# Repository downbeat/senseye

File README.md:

# SensEye

SensEye is a low-power, wireless gaze detection system.

## SensEye v1 and v2

[SensEye v1](SENSEYE_V1.md) is a fully implemented prototype wireless eyetracker system based on cloud offloading and machine learning.  SensEye v2 is the started, incomplete, [but not abandonded](https://github.com/lab11/SensEye-2), second generation eye tracking capture platform, capable of streaming data from two imagers at 29 frames-per-second (FPS) over a pseudo-HTTP 1.0 interface.

## Authors

SensEye v1 is the work of Joe Romeo, Justin Paupore and me, Russ Bielawski.  SensEye v2, insofar as it existed within the time frame of this repository, is my sole, personal work as a Graduate Student Research Assistant (GSRA) of [Prabal Dutta](https://web.eecs.umich.edu/~prabal)'s in 2012-2013.

## Major git Repo Reorganization

The SensEye git repository was, for a long time, in need of serious reorganization.  In addition to reorganization, I took the opportunity to finish a few things (I couldn't resist).

I have done some pretty gnarly hacking on the git repository, up to and including using <a href="https://help.github.com/articles/remove-sensitive-data/">filter-branch</a> to permanently purge irrelevant data which should have never been stored in the source repo in the first place.

**If you have an old SensEye git repository cloned prior to 2015, you must peform a rebase or clone the repo anew.**

## Repository Organization

The root of the SensEye repository is split into `hardware` and `software` subdirectories.  Any technical documentation is intermingled (generally in the form of README files).  Under both `hardware` and `software`, there are three directories: `common`, `v1` and `v2`.  The distinction between what goes in these directories should be clear: SensEye v1 artifacts are found in `v1`, SensEye v2 artifacts are found in `v2` and artifacts which are common to both are in found in `common`.

## Frontend Software

The so called "frontend" software is the software that runs on a PC or smartphone connected to the glasses with Bluetooth (or USB).  Most of the frontend code for SensEye is not v1 or v2 specific, with the exception of the so-called "capture frontends" for each, which receive the data from the capture hardware and output it over stdout according to the Glasses Data Protocol (GDP).  The common frontend code is found in [/software/common/frontends/](software/common/frontends/).  The PC frontend code was written for Linux, but most seems to build and run fine on OS X with OpenCV installed via MacPorts.

### Running the PC Frontend Code

The frontends are connected to one another via [pipes](https://en.wikipedia.org/wiki/Pipeline_%28Unix%29) communicating (unidirectionally) over the Glasses Data Protocol (GDP).  To understand what a particular frontend does, read the help text for that program.  As a simple (and common) example, the following command will capture data from SensEye glasses and both display the images on the screen and record the capture to disk in Glasses Data Exchange Formate (GDF):

    glasses_capture | tee >(glasses_display) | glasses_record -o <path>

#### The SensEye Demo

**Sadly, the demo crashes on OS X.  See [http://code.opencv.org/issues/2846](http://code.opencv.org/issues/2846).**

To run the demo:

    glasses_capture | demo

For a description of how to use the demo, see [http://energy.eecs.umich.edu/wiki/doku.php?id=proj:insight:insight_linux_utils](http://energy.eecs.umich.edu/wiki/doku.php?id=proj:insight:insight_linux_utils).

#### Other platforms

##### Android

When SensEye was conceived, it was envisioned that smartphones would be used as the powerful co-processing device to perform the really processor and memory intensive operations (such as the machine learning classifier).  A simple proof-of-concept capture frontend (called "frame grabber") was developed for Android, and is found in the repository at [/software/v1/capture_frontend/android](software/v1/capture_frontend/android).  Most of the interesting data processing frontend software was written for a Linux PC because it was the easiest way to make the most progress as quickly as possible.

#### Etymology of the Label "Frontend" Software

Admittedly, calling this the "frontend" software seems backwards.  A better name might be "cloud" software, but even that isn't quite evocative enough.  In the usual case, the cloud portion of an offloading application is called the "backend."  However, the situation with offloading *to* a smartphone muddles this conceptually.  Because the feedback to the user (at least in the SensEye prototype) is provided via the front-end software running on a device with a screen.

### Data Processing Interchange Protocol and Frontends

Frontends (for *nix), such as glasses_display, glasses_record and capture_replay, utilize the Glasses Data Protocol (GDP) v1 (or, pre-v1, called v0) to pass data between one another.

During the cleanup of this repository, I took time to formalize the protocol and data exchange (recoreded file on disk) formats.  Glasses Data Protocol (GDP) v1 and Glasses Data Exchange Format (GDF) v1 are both implemented in a C library, libglasses2.  This formalization of the previously not-formal protocol makes as few changes as possible to allow painless adaptation of existing code. 

#### Limitations of the Protocol 

The data processing protocol is fine for exchanging image data between data processing programs (frontends) in grayscale.  However, the protocol lacks any support for color images or scalar data such as the known gaze location, which it really needs in order to support all the non-standard features of the existing frontends in a standardized way.

## Funding

SensEye was supported by the National Science Foundation, NSF Grant 1239341.

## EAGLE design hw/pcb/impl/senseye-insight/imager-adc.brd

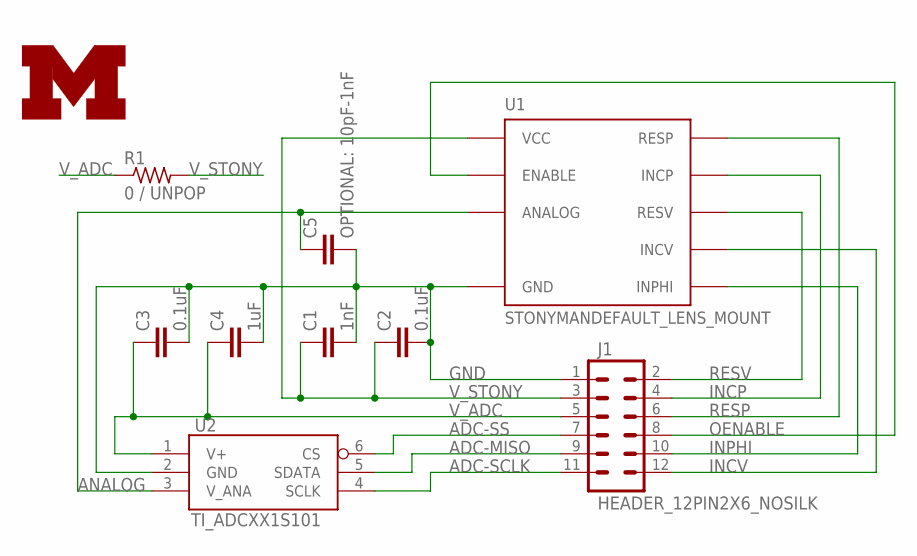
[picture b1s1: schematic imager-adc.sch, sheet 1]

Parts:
C1: 1nF; C0603; DIGIKEY 1276-1916-2-ND
C2, C3: 0.1uF; C0603; DIGIKEY 1276-1012-2-ND
C4: 1uF; C0603; DIGIKEY 1276-1243-2-ND
C5: OPTIONAL: 10pF-1nF; C0603; DIGIKEY 1276-1187-6-ND
J1: HEADER_12PIN2X6_NOSILK; HEADER2X6/0.05IN_NO_SILK; DIGIKEY S9015E-06-ND
R1: 0 / UNPOP; R0603; DIGIKEY 1276-3510-6-ND
U1: STONYMANDEFAULT_LENS_MOUNT; STONYMAN_DEFAULT_LENS
U2: TI_ADCXX1S101; SOT23-6; DIGIKEY ADC121S101CIMF/NOPBDKR-ND
U$1: UMICH_SOLID_SMALL; UMICH_SOLID_75MIL

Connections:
ADC-MISO: J1.9, U2.5 (SDATA)
ADC-SCLK: J1.11, U2.4 (SCLK)
ADC-SS: J1.7, U2.6 (CS)
ANALOG: C5.1, U1.P$8 (ANALOG), U2.3 (V_ANA)
GND: C1.2, C2.2, C3.2, C4.2, C5.2, J1.1, U1.P$1 (GND), U1.P$10 (GND), U2.2 (GND)
INCP: J1.4, U1.P$4 (INCP)
INCV: J1.12, U1.P$6 (INCV)
INPHI: J1.10, U1.P$7 (INPHI)
OENABLE: J1.8, U1.P$9 (ENABLE)
RESP: J1.6, U1.P$3 (RESP)
RESV: J1.2, U1.P$5 (RESV)
V_ADC: C3.1, C4.1, J1.5, R1.1, U2.1 (V+)
V_STONY: C1.1, C2.1, J1.3, R1.2, U1.P$2 (VCC)

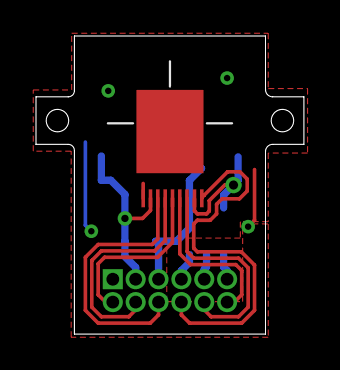
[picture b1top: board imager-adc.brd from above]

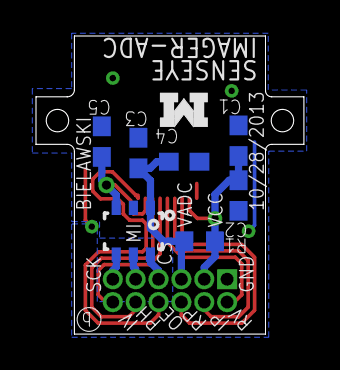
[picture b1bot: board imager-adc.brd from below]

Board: 2 copper layers, 14.9 x 16.6 mm, 10 parts (8 on the bottom side), 13 nets.

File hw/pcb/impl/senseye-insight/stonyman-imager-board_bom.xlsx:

Part | Value | Device | Package | DIGIKEY | Description
C1 | 1nF | C-EUC0603 | C0603 | 1276-1916-2-ND | CAPACITOR, European symbol
C2 | 0.1uF | C-EUC0603 | C0603 | 1276-1012-2-ND | CAPACITOR, European symbol
C3 | 0.1uF | C-EUC0603 | C0603 | 1276-1012-2-ND | CAPACITOR, European symbol
C4 | 1uF | C-EUC0603 | C0603 | 1276-1243-2-ND | CAPACITOR, European symbol
C5 | OPTIONAL: 10pF-1nF | C-EUC0603 | C0603 | 1276-1187-6-ND | CAPACITOR, European symbol
J1 | HEADER_12PIN2X6_NOSILK | HEADER_12PIN2X6_NOSILK | HEADER2X6/0.05IN_NO_SILK | S9015E-06-ND
R1 | 0 / UNPOP | R-US_R0603 | R0603 | 1276-3510-6-ND | RESISTOR, American symbol
U1 | STONYMANDEFAULT_LENS_MOUNT | STONYMANDEFAULT_LENS_MOUNT | STONYMAN_DEFAULT_LENS |  | Centeye Stonyman imager chip
U2 | TI_ADCXX1S101 | TI_ADCXX1S101 | SOT23-6 | ADC121S101CIMF/NOPBDKR-ND | Texas Instruments ADCXX1S101 (ADC081S101, ADC101S101, ADC121S101) Single Channe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

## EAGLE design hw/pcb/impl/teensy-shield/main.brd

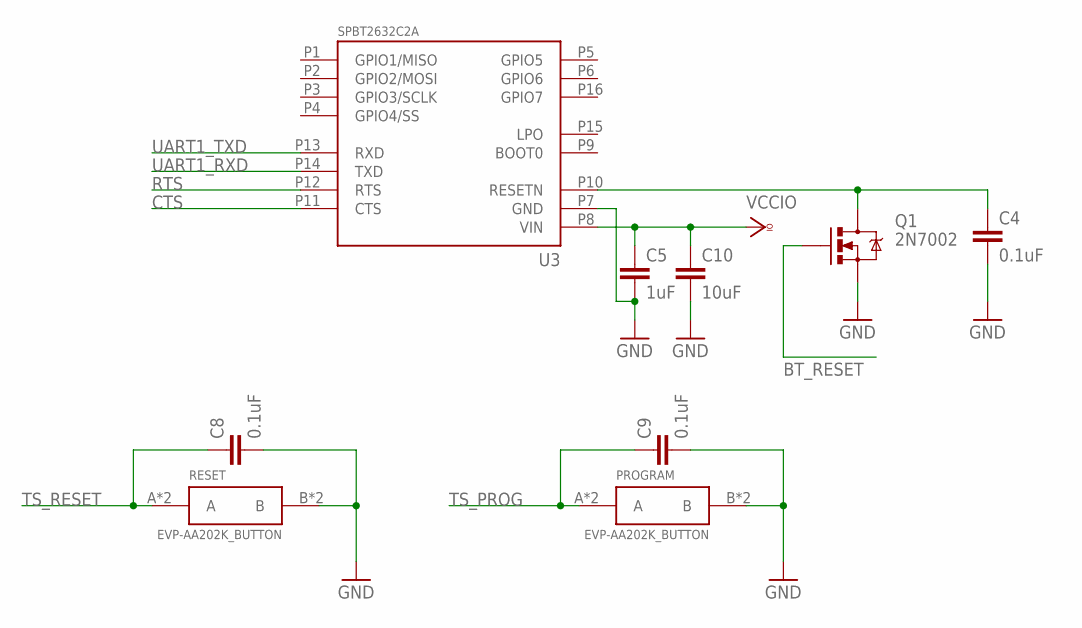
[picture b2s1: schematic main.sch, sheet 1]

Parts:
C4: 0.1uF; C0402
C5: 1uF; C0402
C8, C9: 0.1uF; C0603
C10: 10uF; C0603@1
PROGRAM: EVP-AA202K_BUTTON; EVP-AA202K_4PIN
Q1: 2N7002; SOT23-3
RESET: EVP-AA202K_BUTTON; EVP-AA202K_4PIN
U3: SPBT2632C2A; SPBT2632C2A_16PIN_SMD

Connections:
BT_RESET: Q1.1 (G); also elsewhere on the board
CTS: U3.P11 (CTS); also elsewhere on the board
GND: C4.2, C5.2, C8.2, C9.2, C10.2, PROGRAM.B, PROGRAM.B' (B), Q1.2 (S), RESET.B, RESET.B' (B), U3.P7 (GND); also elsewhere on the board
unnamed: C4.1, Q1.3 (D), U3.P10 (RESETN)
RTS: U3.P12 (RTS); also elsewhere on the board
TS_PROG: C9.1, PROGRAM.A, PROGRAM.A' (A); also elsewhere on the board
TS_RESET: C8.1, RESET.A, RESET.A' (A); also elsewhere on the board
UART1_RXD: U3.P14 (TXD); also elsewhere on the board
UART1_TXD: U3.P13 (RXD); also elsewhere on the board
VCCIO: C5.1, C10.1, U3.P8 (VIN); also elsewhere on the board

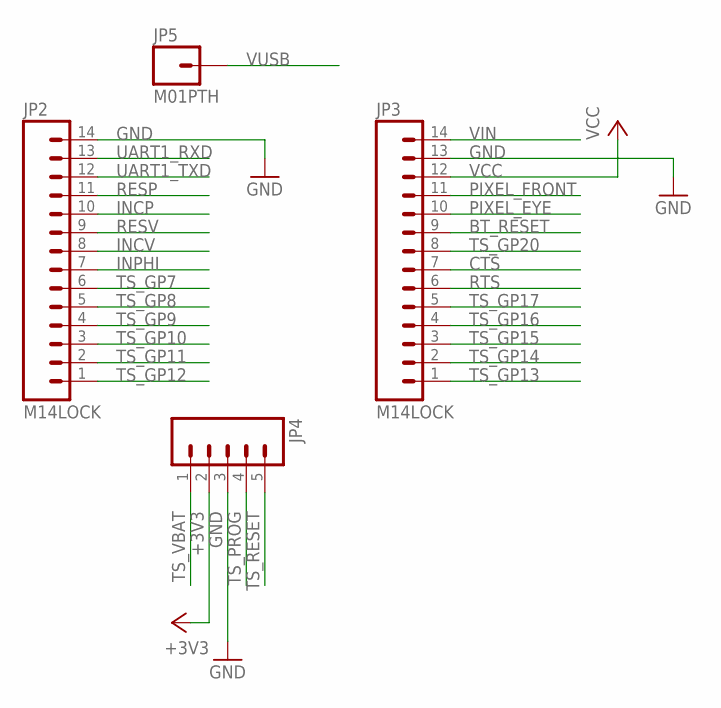
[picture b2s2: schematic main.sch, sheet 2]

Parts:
JP2, JP3: M14LOCK; 1X14_LOCK
JP4: M05LOCK; 1X05_LOCK
JP5: M01PTH; 1X01

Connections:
+3V3: JP4.2
BT_RESET: JP3.9; also elsewhere on the board
CTS: JP3.7; also elsewhere on the board
GND: JP2.14, JP3.13, JP4.3; also elsewhere on the board
INCP: JP2.10
INCV: JP2.8
INPHI: JP2.7
PIXEL_EYE: JP3.10
PIXEL_FRONT: JP3.11
RESP: JP2.11
RESV: JP2.9
RTS: JP3.6; also elsewhere on the board
TS_GP7: JP2.6
TS_GP8: JP2.5
TS_GP9: JP2.4
TS_GP10: JP2.3
TS_GP11: JP2.2
TS_GP12: JP2.1
TS_GP13: JP3.1
TS_GP14: JP3.2
TS_GP15: JP3.3
TS_GP16: JP3.4
TS_GP17: JP3.5
TS_GP20: JP3.8
TS_PROG: JP4.4; also elsewhere on the board
TS_RESET: JP4.5; also elsewhere on the board
TS_VBAT: JP4.1
UART1_RXD: JP2.13; also elsewhere on the board
UART1_TXD: JP2.12; also elsewhere on the board
VCC: JP3.12
VIN: JP3.14; also elsewhere on the board
VUSB: JP5.1; also elsewhere on the board

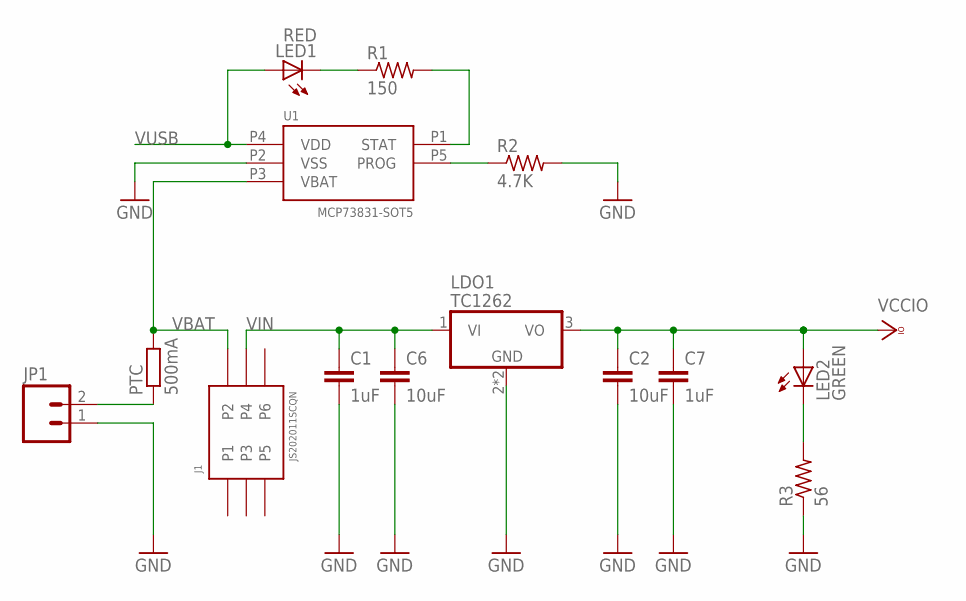
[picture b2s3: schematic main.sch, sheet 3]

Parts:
C1: 1uF; C0603
C2: 10uF; C0603
C6: 10uF; C0603@1
C7: 1uF; C0603@1
J1: JS202011SCQN; JS2020_6PIN_SMT
JP1: M02-JST-2MM-SMT; JST-2-SMD
LDO1: TC1262; SOT223
LED1: RED; CHIPLED_0603
LED2: GREEN; CHIPLED_0603
PTC: 500mA; R0402
R1: 150; R0402
R2: 4.7K; R0402
R3: 56; R0603
U1: MCP73831-SOT5; SOT23-5

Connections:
GND: C1.2, C2.2, C6.2, C7.2, JP1.1, LDO1.2 (GND), LDO1.4 (GND), R2.2, R3.1, U1.P2 (VSS); also elsewhere on the board
unnamed: LED1.C, R1.1
unnamed: R1.2, U1.P1 (STAT)
unnamed: R2.1, U1.P5 (PROG)
unnamed: JP1.2, PTC.1
unnamed: LED2.C, R3.2
VBAT: J1.P2, PTC.2, U1.P3 (VBAT)
VCCIO: C2.1, C7.1, LDO1.3 (VO), LED2.A; also elsewhere on the board
VIN: C1.1, C6.1, J1.P4, LDO1.1 (VI); also elsewhere on the board
VUSB: LED1.A, U1.P4 (VDD); also elsewhere on the board

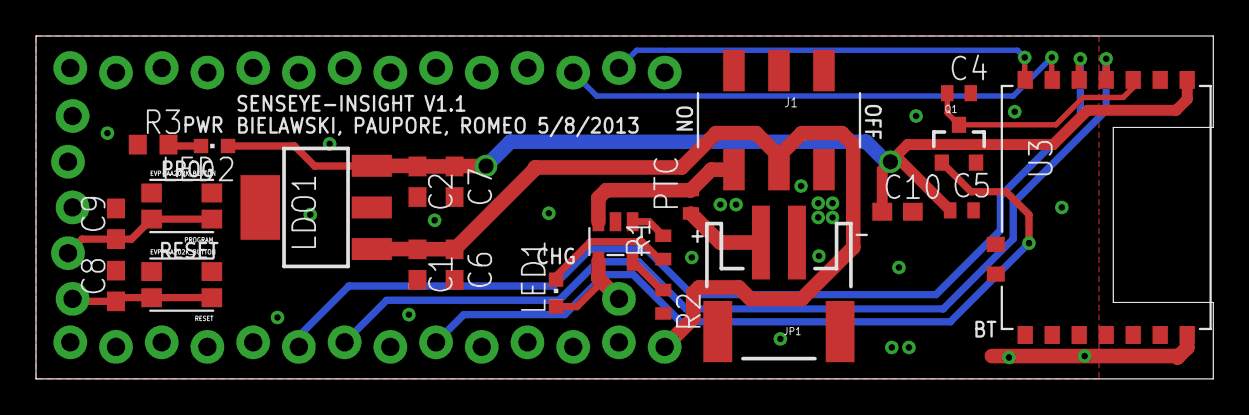
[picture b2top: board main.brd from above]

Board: 2 copper layers, 65.4 x 19.1 mm, 27 parts (0 on the bottom side), 18 nets.

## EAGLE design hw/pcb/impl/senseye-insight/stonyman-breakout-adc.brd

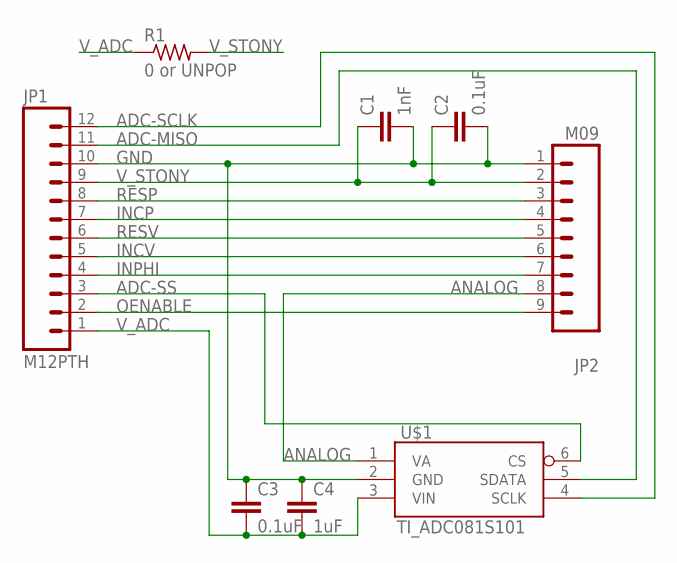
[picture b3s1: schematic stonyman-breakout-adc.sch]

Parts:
C1: 1nF; C0603
C2, C3: 0.1uF; C0603
C4: 1uF; C0603
JP1: M12PTH; 1X12
JP2: M09; 1X09
R1: 0 or UNPOP; R0603
U$1: TI_ADC081S101; SOT23-6

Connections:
ADC-MISO: JP1.11, U$1.5 (SDATA)
ADC-SCLK: JP1.12, U$1.4 (SCLK)
ADC-SS: JP1.3, U$1.6 (CS)
ANALOG: JP2.8, U$1.1 (VA)
GND: C1.2, C2.2, C3.1, C4.1, JP1.10, JP2.1, U$1.2 (GND)
INCP: JP1.7, JP2.4
INCV: JP1.5, JP2.6
INPHI: JP1.4, JP2.7
OENABLE: JP1.2, JP2.9
RESP: JP1.8, JP2.3
RESV: JP1.6, JP2.5
V_ADC: C3.2, C4.2, JP1.1, R1.1, U$1.3 (VIN)
V_STONY: C1.1, C2.1, JP1.9, JP2.2, R1.2

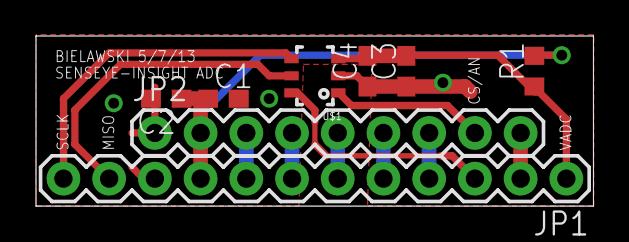
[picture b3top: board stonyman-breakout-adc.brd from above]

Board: 2 copper layers, 31.0 x 9.4 mm, 8 parts (0 on the bottom side), 13 nets.

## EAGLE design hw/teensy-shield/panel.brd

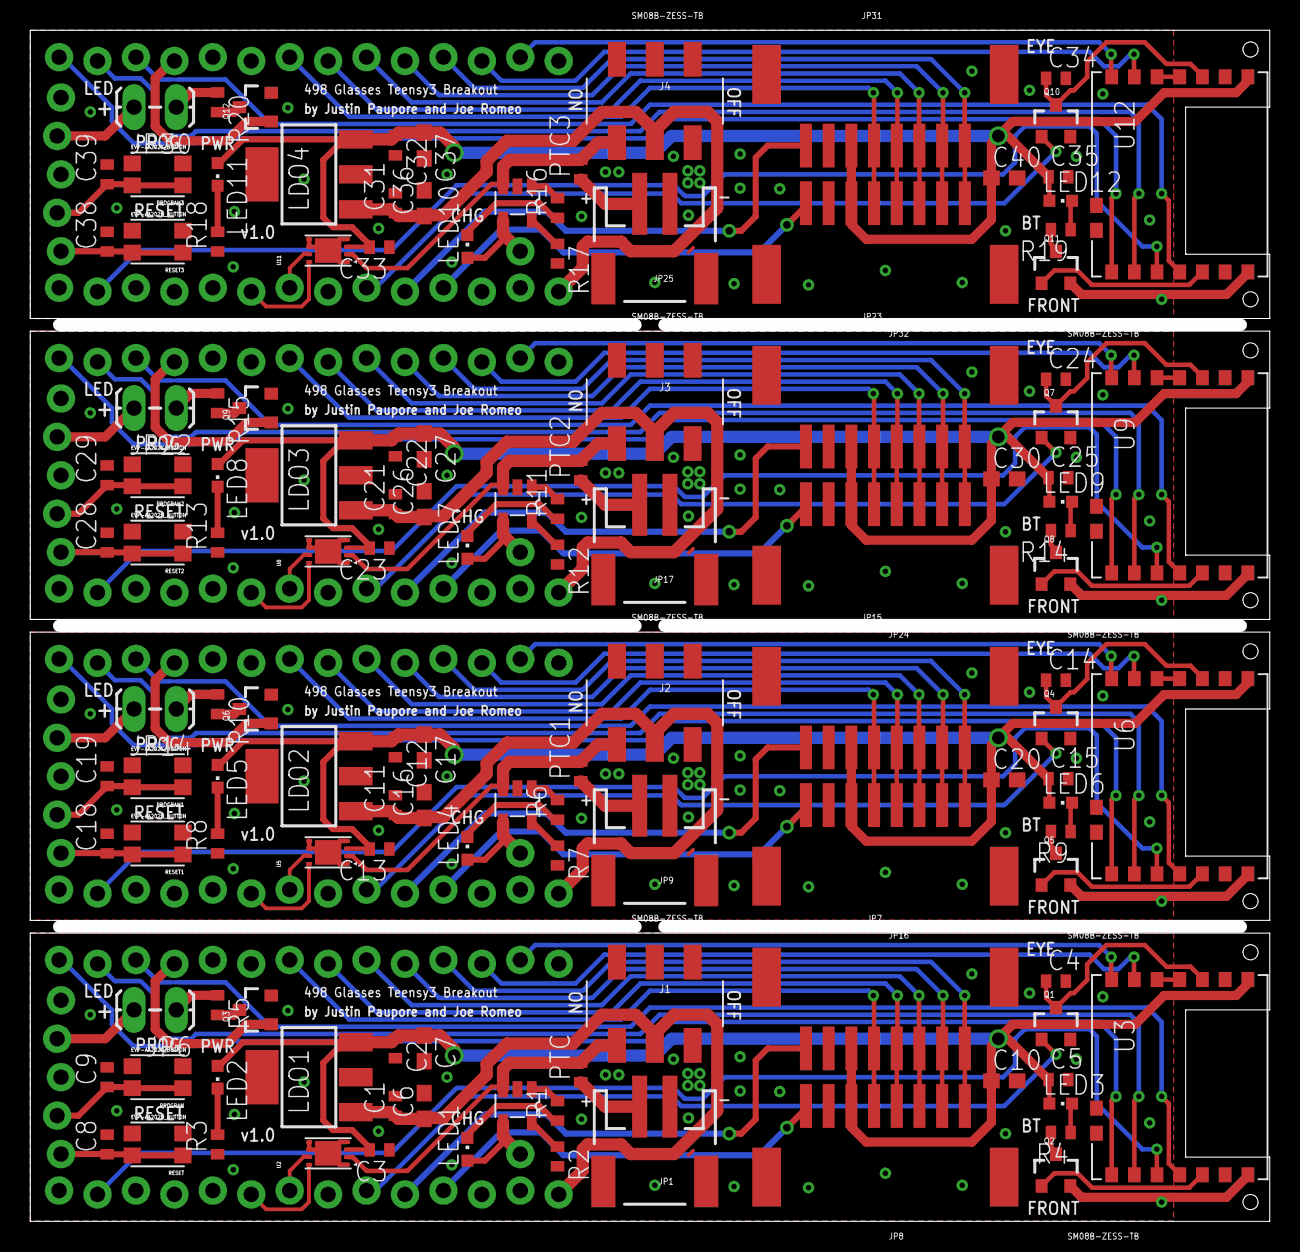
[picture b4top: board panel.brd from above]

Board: 2 copper layers, 81.1 x 77.9 mm, 148 parts (0 on the bottom side), 148 nets.

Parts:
C1, C2, C3, C5, C11, C12, C13, C15, C21, C22, C23, C25, C31, C32, C33, C35: 1uF; C0402
C4, C8, C9, C14, C18, C19, C24, C28, C29, C34, C38, C39: 0.1uF; C0402
C6, C7, C10, C16, C17, C20, C26, C27, C30, C36, C37, C40: 10uF; C0603
J1, J2, J3, J4: JS202011SCQN; JS2020_6PIN_SMT
JP1, JP9, JP17, JP25: JST-2-SMD
JP2, JP3, JP10, JP11, JP18, JP19, JP26, JP27: M14LOCK; 1X14_LOCK
JP4, JP12, JP20, JP28: 1X05_LOCK
JP5, JP13, JP21, JP29: M01PTH; 1X01
JP6, JP14, JP22, JP30: LED; 1X02_LOCK_LONGPADS
JP7, JP8, JP15, JP16, JP23, JP24, JP31, JP32: SM08B-ZESS-TB; SM08B_8PIN_SMD
LDO1, LDO2, LDO3, LDO4: TC1262; SOT223
LED1, LED4, LED7, LED10: RED; CHIPLED_0603
LED2, LED5, LED8, LED11: GREEN; CHIPLED_0603
LED3, LED6, LED9, LED12: BLUE; CHIPLED_0603
PROGRAM, PROGRAM1, PROGRAM2, PROGRAM3: EVP-AA202K_BUTTON; EVP-AA202K_4PIN
PTC, PTC1, PTC2, PTC3: 500mA; R0402
Q1, Q2, Q3, Q4, Q5, Q6, Q7, Q8, Q9, Q10, Q11, Q12: 2N7002; SOT23-3
R1, R6, R11, R16: 150; R0402
R2, R7, R12, R17: 4.7K; R0402
R3, R4, R8, R9, R13, R14, R18, R19: 56; R0402
R5, R10, R15, R20: DNI; R0402
RESET, RESET1, RESET2, RESET3: EVP-AA202K_BUTTON; EVP-AA202K_4PIN
U1, U4, U7, U10: MCP73831-SOT5; SOT23-5
U2, U5, U8, U11: MAX17040-TDFN; TDFN_8PIN
U3, U6, U9, U12: SPBT2632C2A; SPBT2632C2A_16PIN_SMD

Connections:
+3V1: JP12.2, JP14.2
+3V2: JP20.2, JP22.2
+3V3: JP4.2, JP6.2
+3V4: JP28.2, JP30.2
BT_RESET: JP3.9, Q1.1
BT_RESET1: JP11.9, Q4.1
BT_RESET2: JP19.9, Q7.1
BT_RESET3: JP27.9, Q10.1
GND: C1.2, C2.2, C3.1, C4.2, C5.2, C6.2, C7.2, C8.2, C9.2, C10.2, JP1.1, JP2.14, JP3.13, JP4.3, JP7.P7, JP8.P2, LDO1.2, LDO1.4, PROGRAM.B, PROGRAM.B', Q1.2, Q2.2, Q3.2, R2.2, R3.1, RESET.B, RESET.B', U1.P2, U2.EP, U2.P1, U2.P4, U2.P5, U2.P6, U3.P7
GND1: C11.2, C12.2, C13.1, C14.2, C15.2, C16.2, C17.2, C18.2, C19.2, C20.2, JP9.1, JP10.14, JP11.13, JP12.3, JP15.P7, JP16.P2, LDO2.2, LDO2.4, PROGRAM1.B, PROGRAM1.B', Q4.2, Q5.2, Q6.2, R7.2, R8.1, RESET1.B, RESET1.B', U4.P2, U5.EP, U5.P1, U5.P4, U5.P5, U5.P6, U6.P7
GND2: C21.2, C22.2, C23.1, C24.2, C25.2, C26.2, C27.2, C28.2, C29.2, C30.2, JP17.1, JP18.14, JP19.13, JP20.3, JP23.P7, JP24.P2, LDO3.2, LDO3.4, PROGRAM2.B, PROGRAM2.B', Q7.2, Q8.2, Q9.2, R12.2, R13.1, RESET2.B, RESET2.B', U7.P2, U8.EP, U8.P1, U8.P4, U8.P5, U8.P6, U9.P7
GND3: C31.2, C32.2, C33.1, C34.2, C35.2, C36.2, C37.2, C38.2, C39.2, C40.2, JP25.1, JP26.14, JP27.13, JP28.3, JP31.P7, JP32.P2, LDO4.2, LDO4.4, PROGRAM3.B, PROGRAM3.B', Q10.2, Q11.2, Q12.2, R17.2, R18.1, RESET3.B, RESET3.B', U10.P2, U11.EP, U11.P1, U11.P4, U11.P5, U11.P6, U12.P7
I2C_SCL: JP3.7, U2.P7
I2C_SCL1: JP11.7, U5.P7
I2C_SCL2: JP19.7, U8.P7
I2C_SCL3: JP27.7, U11.P7
I2C_SDA: JP3.6, U2.P8
I2C_SDA1: JP11.6, U5.P8
I2C_SDA2: JP19.6, U8.P8
I2C_SDA3: JP27.6, U11.P8
INCP: JP2.10, JP7.P2, JP8.P7
INCP1: JP10.10, JP15.P2, JP16.P7
INCP2: JP18.10, JP23.P2, JP24.P7
INCP3: JP26.10, JP31.P2, JP32.P7
INCV: JP2.8, JP7.P4, JP8.P5
INCV1: JP10.8, JP15.P4, JP16.P5
INCV2: JP18.8, JP23.P4, JP24.P5
INCV3: JP26.8, JP31.P4, JP32.P5
INPHI: JP2.7, JP7.P5, JP8.P4
INPHI1: JP10.7, JP15.P5, JP16.P4
INPHI2: JP18.7, JP23.P5, JP24.P4
INPHI3: JP26.7, JP31.P5, JP32.P4
IR_LED: JP2.4, Q3.1
IR_LED1: JP10.4, Q6.1
IR_LED2: JP18.4, Q9.1
IR_LED3: JP26.4, Q12.1
unnamed: LED1.C, R1.1
unnamed: R1.2, U1.P1
unnamed: R2.1, U1.P5
unnamed: JP1.2, PTC.1
unnamed: LED2.C, R3.2
unnamed: U3.P11, U3.P12
unnamed: C4.1, Q1.3, U3.P10
unnamed: Q2.1, U3.P5
unnamed: LED3.C, R4.1
unnamed: Q2.3, R4.2
unnamed: JP6.1, R5.1
unnamed: Q3.3, R5.2
unnamed: U6.P11, U6.P12
unnamed: C14.1, Q4.3, U6.P10
unnamed: Q5.1, U6.P5
unnamed: LED6.C, R9.1
unnamed: Q5.3, R9.2
unnamed: JP14.1, R10.1
unnamed: Q6.3, R10.2
unnamed: R6.2, U4.P1
unnamed: R7.1, U4.P5
unnamed: JP9.2, PTC1.1
unnamed: LED5.C, R8.2
unnamed: LED4.C, R6.1
unnamed: U9.P11, U9.P12
unnamed: C24.1, Q7.3, U9.P10
unnamed: Q8.1, U9.P5
unnamed: LED9.C, R14.1
unnamed: Q8.3, R14.2
unnamed: JP22.1, R15.1
unnamed: Q9.3, R15.2
unnamed: R11.2, U7.P1
unnamed: R12.1, U7.P5
unnamed: JP17.2, PTC2.1
unnamed: LED8.C, R13.2
unnamed: LED7.C, R11.1
unnamed: U12.P11, U12.P12
unnamed: C34.1, Q10.3, U12.P10
unnamed: Q11.1, U12.P5
unnamed: LED12.C, R19.1
unnamed: Q11.3, R19.2
unnamed: JP30.1, R20.1
unnamed: Q12.3, R20.2
unnamed: R16.2, U10.P1
unnamed: R17.1, U10.P5
unnamed: JP25.2, PTC3.1
unnamed: LED11.C, R18.2
unnamed: LED10.C, R16.1
PIXEL_EYE: JP3.10, JP7.P8
PIXEL_EYE1: JP11.10, JP15.P8
PIXEL_EYE2: JP19.10, JP23.P8
PIXEL_EYE3: JP27.10, JP31.P8
PIXEL_FRONT: JP3.11, JP8.P1
PIXEL_FRONT1: JP11.11, JP16.P1
PIXEL_FRONT2: JP19.11, JP24.P1
PIXEL_FRONT3: JP27.11, JP32.P1
RESP: JP2.11, JP7.P1, JP8.P8
RESP1: JP10.11, JP15.P1, JP16.P8
RESP2: JP18.11, JP23.P1, JP24.P8
RESP3: JP26.11, JP31.P1, JP32.P8
RESV: JP2.9, JP7.P3, JP8.P6
RESV1: JP10.9, JP15.P3, JP16.P6
RESV2: JP18.9, JP23.P3, JP24.P6
RESV3: JP26.9, JP31.P3, JP32.P6
SPI_CS: JP2.3, U3.P4
SPI_CS1: JP10.3, U6.P4
SPI_CS2: JP18.3, U9.P4
SPI_CS3: JP26.3, U12.P4
SPI_MISO: JP2.1, U3.P1
SPI_MISO1: JP10.1, U6.P1
SPI_MISO2: JP18.1, U9.P1
SPI_MISO3: JP26.1, U12.P1
SPI_MOSI: JP2.2, U3.P2
SPI_MOSI1: JP10.2, U6.P2
SPI_MOSI2: JP18.2, U9.P2
SPI_MOSI3: JP26.2, U12.P2
SPI_SCK: JP3.2, U3.P3
SPI_SCK1: JP11.2, U6.P3
SPI_SCK2: JP19.2, U9.P3
SPI_SCK3: JP27.2, U12.P3
TS_PROG: C9.1, JP4.4, PROGRAM.A, PROGRAM.A'
TS_PROG1: C19.1, JP12.4, PROGRAM1.A, PROGRAM1.A'
TS_PROG2: C29.1, JP20.4, PROGRAM2.A, PROGRAM2.A'
TS_PROG3: C39.1, JP28.4, PROGRAM3.A, PROGRAM3.A'
TS_RESET: C8.1, JP4.5, RESET.A, RESET.A'
TS_RESET1: C18.1, JP12.5, RESET1.A, RESET1.A'
TS_RESET2: C28.1, JP20.5, RESET2.A, RESET2.A'
TS_RESET3: C38.1, JP28.5, RESET3.A, RESET3.A'
UART1_RXD: JP2.13, U3.P14
UART1_RXD1: JP10.13, U6.P14
UART1_RXD2: JP18.13, U9.P14
UART1_RXD3: JP26.13, U12.P14
UART1_TXD: JP2.12, U3.P13
UART1_TXD1: JP10.12, U6.P13
UART1_TXD2: JP18.12, U9.P13
UART1_TXD3: JP26.12, U12.P13
VBAT: J1.P2, PTC.2, U1.P3, U2.P2
VBAT1: J2.P2, PTC1.2, U4.P3, U5.P2
VBAT2: J3.P2, PTC2.2, U7.P3, U8.P2
VBAT3: J4.P2, PTC3.2, U10.P3, U11.P2
VCCIO: C2.1, C3.2, C5.1, C7.1, C10.1, JP7.P6, JP8.P3, LDO1.3, LED2.A, LED3.A, U2.P3, U3.P8
VCCIO1: C12.1, C13.2, C15.1, C17.1, C20.1, JP15.P6, JP16.P3, LDO2.3, LED5.A, LED6.A, U5.P3, U6.P8
VCCIO2: C22.1, C23.2, C25.1, C27.1, C30.1, JP23.P6, JP24.P3, LDO3.3, LED8.A, LED9.A, U8.P3, U9.P8
VCCIO3: C32.1, C33.2, C35.1, C37.1, C40.1, JP31.P6, JP32.P3, LDO4.3, LED11.A, LED12.A, U11.P3, U12.P8
VIN: C1.1, C6.1, J1.P4, JP3.14, LDO1.1
VIN1: C11.1, C16.1, J2.P4, JP11.14, LDO2.1
VIN2: C21.1, C26.1, J3.P4, JP19.14, LDO3.1
VIN3: C31.1, C36.1, J4.P4, JP27.14, LDO4.1
VUSB: JP5.1, LED1.A, U1.P4
VUSB1: JP13.1, LED4.A, U4.P4
VUSB2: JP21.1, LED7.A, U7.P4
VUSB3: JP29.1, LED10.A, U10.P4

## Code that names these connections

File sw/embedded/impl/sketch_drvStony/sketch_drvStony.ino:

#include "stony.h"


const char PIN_LED = 13;

const char PIN_RESP = 8;
const char PIN_INCP = 7;
const char PIN_RESV = 6;
const char PIN_INCV = 5;
const char PIN_INPHI = 4;
const char PIN_ANALOG = A0;

const unsigned long BAUDRATE = 115200;


camera stonycam;
// for bluetooth over UART
//HardwareSerial Uart = HardwareSerial();


void getCmd(char*);


void setup()
{
  pinMode(13,OUTPUT);
  digitalWrite(PIN_LED,1);

  Serial.begin(BAUDRATE);

  (void)stonycam.init(PIN_RESP, PIN_INCP, PIN_RESV, PIN_INCV, PIN_INPHI, PIN_ANALOG); // raw: for 5v
  //(void)stonycam.init(PIN_RESP, PIN_INCP, PIN_RESV, PIN_INCV, PIN_INPHI, PIN_ANALOG,35,50,50,1,1); // amp: for 3v3
}

void loop()
{
  char cmd;

  while(!Serial.available());

  digitalWrite(PIN_LED,0);

  getCmd(&cmd);

  switch(cmd)
  {
    case 'Z':
      stonycam.chipToMatlab();
      break;
    case '?':
    default:
      Serial.println("Z: MATLAB chip"); 
      delay(50);
      break;
  }

  digitalWrite(PIN_LED,1);
}

// russ: this is a (simplified) clone of ArduEyeGUIClass::getCommand from the ArduEye_GUI library
// for some reason, sscanf is blowing up my linker (probably a bug in teensyduino for teensy3),
// so I just removed the argument processing (which I didn't need anyway)
void getCmd(char *command)
{
  char cmdbuf[11];
  unsigned char i;

  // initialize
  for (i=0; i<11; ++i)
    cmdbuf[i] = 0;
  i = 0;
  // delay to ensure that all stuff is sent through serial port
  delay(100);
  // load cmdbuf
  while (Serial.available() && i<10) {
    cmdbuf[i] = Serial.read();
    i++;
  }
  // clear end of array
  cmdbuf[10]=0;
  // clear rest of buffer
  while (Serial.available())
    ;
  // get command
  *command = cmdbuf[0];
}

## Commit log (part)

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2012-11-26 actually checking in changes to dual variant
    actually checking in the changes to dualcameracapture.ino that make it
    have some of the (cosmetic) changes to cameracapture.ino
2012-11-26 upping capture speed with digitalWriteFast
    changed all digitalWrite calls to digitalWriteFast calls, which speeds
    up these programs quite a bit.
2012-11-28 removed and ignored binary for glassescapstream
2012-11-28 some simple fixes to the t&m suite
2012-12-06 This is the glasses replaystream color hack
    It is what the name says. If you find color images somewhere use this.
    The eye detect stuff saves color files with puple predictions marked
    (not very nice).
2012-12-06 the demo now saves each training set!
2012-12-08 glassesreplaystream now works without an FPS file
2012-12-11 added the deployment keys into the repo
    anyone who posses the private key has read-only access to the repo.
2012-12-19 removed opencv_pc directory in favor of linux
    removed the sw/opencv_pc directory in favor of the sw/linux directory
    which I had previously created and forgotten about.
2012-12-26 glassescapstream: specify debug on command line
    glassescapstream now accepts a command line argument to enable debug
    output instead of requiring a recompile.
2012-12-26 gazesetgroundtruth: junk frames also marked bad
    gazesetgroundtruth: all junk frames are also automatically marked as bad
2012-12-26 oldmonolithicglassescapture: fix compiler warnings
    fixed the 3 compiler warnings when compiling oldmonolithicglassescapture
2012-12-28 glassescapstream: updated help text
    updated the help text for glassescapstream removing the line about using
    the ESC key to quit (which was never really true)
2012-12-28 made hw/impl directory and moved eagle files there
    created a hw/impl directly which mirrors the rest of the repo and moved
    the eagle files there (specifically, the teensy-shield)
2013-01-10 fixed usb_breadboard_dualcameracapture/Makefile
    fixed usb_breadboard_dualcameracapture/Makefile to have the correct
    project name
2013-02-07 added FAIR_WARNING file about renaming linux utils
    added a FAIR_WARNING file to /sw/linux/impl which warns that one day the
    file names will change all at once.
2013-02-11 added more version comments to AdcCap.v
    added a version comment to AdcCap.v for 1.00, which is the finished and
    working driver for the TI ADC081S101
2013-02-26 got capture_linux project working with libero 10
    got capture_linux project working with libero 10. I had to install
    Libero 9 take a screenshot of the I/O assignments and manually copy
    those settings over to the Libero 10 project.
2013-02-26 changed permissions, most of the repo was modified
    changed file permissions and now most of the repo thinks it was changed.
    so, I'm checking it in! marking ALL files as not executable. Some
    files like ardueyectrl.py or seriallistener.py should actually be
    executable. remark them as such when the time comes that you need to do
    so.
2013-02-26 renamed AdcCap.v to adc081s101.v in both projs
    renamed AdcCap.v to adc081s101.v in both projs, capture and meyesight
2013-03-01 replaced some verilog in capture proj w symlinks
    replaced some verilog files (stonyman.v and adc081s101.v) in capture
    proj with symlinks to the same files in the meyesight projects.
2013-03-04 reorganized smartfusion directory
    reorganized smartfusion directory to have the libero projects in their
    own subdirectory. there will be a new uclinux directory for uClinux
    development work.
2013-03-04 insight-serv can discriminate good vs bad requests
    insight-serv can discriminate good vs bad requests (a good request
    starts with the string "GET" and the rest is ignored). it issues no
    responses right now
2013-03-06 completed working stonyman interface over the APB
    completed working stonyman interface over the APB. it's not beautiful
    or complete, but it works. the program stonyman-apb3-test will kick off
    a camera capture and grab as much data as comes (the correct number of
    bytes is received).
2013-03-22 added the exported I/O constraint file
    unfortunately, the tool does not keep this file up to date in text
    format, and it needs to be manually exported, so it is not guaranteed to
    stay in sync with the rest of the project.
2013-03-22 updated insight-serv to use a mask
    it's currently using the nomask mask, but the feature is added. Now I
    need to compute a calibration mask for the camera I am using (#12). It
    should be noted that the Makefile is rather brittle in it's support
    (it uses a relative path within the repo which could change)
2013-03-26 final cleanup in glassescapwebsock
2013-03-30 doubled FIFO macro size in libero
    from 4096 to 8192
2013-05-07 added the start of my senseye-insight PCB work
    it will include the next generation PCB. for now it is merely the small
    ADC boards for attaching to the Stonyman breakout boards.
2013-05-08 added one more extra piece of GND routing
2013-05-08 added my name, date and comment text
2013-05-08 removed all the stuff we're not using from board
    The fuel gauge IC, the crummy camera JST connectors, everything
2013-05-23 fixed stonyman.v to use correct init vals
    it was hardcoded to use the 3V3 values, but I fixed it.
2013-05-28 added two 3.3V masks for camera 3
    computed with the teensy platform, not the smartfusion platform
2013-06-26 renamed trip... to tripledisplayfromwebsock, pt 1
    the new name gives a better impression of the temporary nature of the
    utility (which will definitely be merged into a 'displayandsave' binary
    soon)
2013-06-26 removed more dead code
    the "scaleduploc" IplImage pointers have been removed.
2013-07-09 updated libero project to run APB at 40MHz
    double the speed of previously (20MHz). The clock subsystem still runs
    at 20MHz (including most of the stonyman logic in stonyman.v)
2013-07-30 added spinlocks to the stonyman driver LKM
    spinlocks were added in stonyman.c to protect some of the shared image
    buffer metadata (shared between stonyman_read and stonyman_interrupt).
    the code is still pretty inefficient and only supports one camera.
2013-08-02 added Stonyman part to senseye eagle library
    Also, somehow, the changes to the ST SPBT2632 and the added TI
    ADC081S101 part were lost from the lbr file. I added those back in
    (although, I manually re-did the SPBT2632 change, so it is not the same
    as the Insight V1.1 board I ran)
2013-08-13 moved two caps to make bottom ground plane connect
2013-08-14 moved lens mount holes into near perfect spots
    just copied CentEye's spacing
2013-08-14 added stopmask to wirebond pads in stonyman part
2013-08-15 changed senseye-serv output while sending frames
    there is only a frame complete message now, which allows it to take less
    time during frame transmission.
2013-08-16 added GND trace between the caps and edge of board
    The polygone for the GND plane didn't fill this in, but there was room,
    and I think it belonged there
2013-08-20 added more space between headers and lens mount
    now the tDocu layers of the headers and the lens mount do not overlap at
    all.
2013-08-21 renamed adc081s101.v to adcxx1s101.v, pt 2
    updated libero to handle this new file/module name. also, made minimal
    modifications to adcxx1s101.v (just the basics)
2013-08-21 renamed libero project from insight to senseye
    this has been a long time coming
2013-08-22 libero changes for last commit (control groups)
    these are the changes to libero file which go along with the previous
    commit about the independent control groups in stonyman_apb3
2013-08-22 LKM driver multi-cam finish interrupts support
    starting multi-cam support by supporting capture done interrupts for
    every camera. this means that each camera is expected to be part of its
    own control group (simultaneous capture of multiple cameras will not be
    supported in the driver for now). each camera now has two GPIO
    interrupts, a capture done interrupt and a high water interrupt. there
    is also a lot of cleanup in the GPIO defines.
2013-08-28 stonyman_interrupt calculates camidx smarter
    it is now a mathematical operation instead of a loop. it should be
    faster in theory, at least for higher camera indices, because it is now
    a set number of instructions (instead of a loop with a break statement).
2013-09-09 fixed a hard to spot bug in tripledisplay...
    The bug confused FRAME_X_Y with FRAME_LEN in unpacking the stream image
    data into the OpenCV image data formats. It was probably a hold-over
    from the dual scanline format from the InSight/SensEye v1 and earlier
    glasses.
2013-09-09 support senseye-serv sending numcams response
    this is the exected first response for stream mode, and it is finally
    supported in senseye-serv (and glassescapwebsock as well)
2013-10-03 deleted libero project 'capture'
2013-10-28 added larger via with soldermask for ANALOG
    this is a more accessable test point for the ANALOG signal. It doesn't
    alter the board design much, it's just a tad bigger. Signals were
    re-routed around it.
    Also expanded the ground planes to fill in the area under the ADC.
2013-10-28 created stonyman-imager-board.cam
    forked 2LPlus-Sunstone.cam to create stonyman-imager-board.cam. The
    stonyman-imager-board.cam reverses top and bottom when generating gerber
    files.
2013-10-31 renamed stonyman-imager-board to imager-adc, pt 2
    actually changing files now. reopened and closed eagle.epf. updated
    doc/.gitignore and doc/create-pdf.sh. also, updated 2 gerber files by
    hand.
2013-10-31 updated gerbers and board document
2015-01-10 Changed .deploymentkeys/readme.md to Markdown
    Updated the contents of .deploymentkeys/readme.md to actually use
    Markdown. Added a comment acknowleding that the private key contained
    herein is as expected.
2015-01-20 Moved SensEye v1 embedded sw to new location.
    Renamed the embedded software directories and files from their old
    location to the new location for reorganization.
2015-01-20 Added README to Android directory.
    Added README to Android directory to explain the status of what is found
    within that directory.
2015-01-20 Slight change in organization in /v1/hw
    Created a directory specifically to hold the Eagle files within the
    eagle_pcb directory.
2015-01-20 Moved glassescapwebsock.c to new location.
    Moved glassescapwebsock.c to the new location for reorganization. This
    is the capture_frontend for v2 and it is new located in
    /v2/sw/capture_frontend/linux.
2015-01-31 Added an OS X makefile.
    Added a dedicated makefile for OS X. It assumes you use OpenCV
    installed through MacPorts.
2015-02-06 Copied glasses.h/c to glasses_util.h/c.
    Copied glasses.h/c to glasses_util.h/c in libglasses. The functionality
    is duplicated for now, but that's only because legacy implementations
    still refernce the glasses.h file.
2015-02-10 Deprecated glasses.h/c.
    Deprecated glasses.h/c in favor of glasses_util.h/c and
    glasses_proto.h/c. getch(...) and peek(...) along with
    asdfasdfasdfadsss
    gutil_read_char(...) and gutil_read_until(...) have been completelysssss
    removed from the glasses library. The readchar(...) and
    readuntilchar(...) functionality is now found in glasses_proto.c, which
2015-02-15 Fixed gdp_read_frame(...) in glasses_proto.c.
    Fixed gdp_read_frame(...) to return correct number of bytes in
    non-scanline mode.
    I'm calling this fix 1.00.01 (which was already committed).
2015-03-19 Renamed the wirebonding document (pt 1).
2015-03-19 Added README.md for SensEye wirebonding doc.
2015-03-20 Created platform agnostic cvEyeTracker Makefile.
    Created platform agnostic cvEyeTracker Makefile. Also commented out an
    unnecessary include in cvEyeTracker.c.
2015-03-20 Renamed cvEyeTracker README to README.md, pt 2.
    This pt 2 commit includes the actual file changes.
2015-03-21 Updated all frontends for easier OS X support.
    A few files which utilized clock checking functionality required
    changes. Otherwise, the changes are to makefiles and .gitignore files.
2015-04-13 Added .dSYM entries for some .gitignore files.
2015-04-13 Renamed v1 glassescapture to glasses_capture pt 2.
    The actual file changes to Makefile and .gitignore.
2015-05-06 Renamed sw to software and hw to hardware.
2015-05-13 Renamed imager-adc.pdf README.md to README.
2015-05-13 Renamed eagle_pcb/doc to schematic_and_layout_pdf.
2015-05-21 Many improvements to SENSEYE_V1.md.
2015-05-21 Added the uCLinux project to the repo.
    I have had this for a long time, but it never got placed in the
    repository.
2015-05-21 Removed mask include from senseye-serv.c.
    It wasn't being used.
2015-05-21 Added a still frame to the README.md.
2015-05-30 Reworded README slightly.
2015-07-07 Reordered and reworded README.md and SENSEYE_V1.md

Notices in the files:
parts and their libraries:
SparkFun-Connectors: Licensing: CC v3.0 Share-Alike You are welcome to use this library for commercial purposes.
